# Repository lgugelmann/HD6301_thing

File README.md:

# Exploring the HD6301V1

I recently received a few samples of a Hitachi `HD6301V1` in a DIP-40
package. It's a 1MHz 8bit CPU derived from the Motorola 6801 with a few extra
instructions. It has an onboard mask-programmed 4k ROM, 128 bytes RAM, and 4 I/O
ports that can be used as some combination of data or address bus, or I/O
lines. It also comes with an onboard serial interface. Overall it's a really
neat chip!

- The datasheet for the HD6301v1 can be found
e.g. [here](https://pdf1.alldatasheet.com/datasheet-pdf/view/87402/HITACHI/HD6301V1.html).
- An _extensive_ handbook for the entire Hitachi 6301/6303 series of CPUs,
including copies of all datasheets, can be found on
[archive.org](https://archive.org/details/bitsavers_hitachidateriesHandbook1989_54281821).

This repository contains schematics and code to build a retro-inspired computer
around this chip. The idea is to build this off of modular components and a
shared bus so we can start small and build up piece by piece.

Currently I have a working device with Arduino-like ease of programmability, PS2
keyboard input, HDMI video output. It's complete enough for a working 'Snake'
clone that can be played over both serial console and video out.

## Getting started on a breadboard

The architecture is quite simple and similar to other 8-bit CPUs like
the 6502. There is one 16-bit address bus, one 8-bit data bus, a clock line, a
read/write line, and an interrupt line.

One way in which this chip departs from e.g. a 6502 is that it has several
different 'modes' that affect the memory layout and external buses. Mode
selection is done at startup using the first 3 lines of port 2. After startup
these lines can be reused for other purposes if desired. Mode 1
(non-multiplexed) breaks out all 16 address and 8 data lines. Mode 5 reduces the
external address bus to 8 lines. Mode 0/2/4/6 multiplex the data bus: at the
beginning of the cycle the 8 low address bits are presented, then an address
latch signal fires, then the 8 data bits are set. This frees up one 8-bit port
for I/O. Mode 7 has no external buses at all. Mode 0/5/6/7 map the internal ROM
to the top of the address space. It's inaccessible in 1/2/4. Mode 0 ('test
mode') has a special handling for the first read of the startup vector addresses
at $FFFE/$FFFF: instead of reading them from ROM (as it would in any subsequent
read) they are read over the external bus. This allows one to override the
ROM-interal startup vector while still keeping it accessible otherwise.

By selecting mode 1 at startup it's easy to get this chip to work on a
breadboard by just adding some external parallel RAM / ROM with a bit of address
decoding to select which one to access.

The chip has an internal 4x clock-divider. To get it to run at the max 1MHz you
need a 4MHz oscillator. I had no stability issues on a breadboard even at max
frequency.

The chip requires a minimum 100kHz to run (400kHz oscillator). Going below makes
it unstable.

## Random hardware notes

This is a collection of random notes about the hardware that are either
well-hidden in the datasheet or not documented at all.

- The IRQ line is not specified to be open-drain. It's likely not.
- The reset and standby pins are drawn with Schmitt-trigger inputs in the
  datasheet.
- The datasheet recommends 74'373 chips to latch the address bits in multiplexed
  mode. The '573 is probably a better choice for layout reasons as it has the
  same functionality but instead of having in/out pins next to each other it has
  all 8 inputs on one side and the 8 outputs on the other.
- P21 is not a general purpose I/O pin (even after mode selection). It is either
  a general input, or timer output.
- The mode selection / P2 multiplexing circuit in the datasheet would probably
  not work with a modern '4053 chip. The one in the datasheet has minimum
  switching times higher than the required hold times on the mode selection
  pins. Modern '4053 are faster.
- Reset and power-up are a bit finicky. The datasheet says reset must be held
  low for at least 20ms at power-on time. That's good advice. Without the wait
  time the MCU seems to start working a hair before the power rail reaches
  3V. The clock and data / address lines have their 'high' bits at that voltage
  too. At that point in time a typical 5V ROM might not even have powered up yet
  and you get all sorts of fun non-deterministic behavior. Something like a
  Diodes Inc. `APX811-46` is a great way to satisfy that requirement as it keeps
  reset low after power-up for 100-200ms.  Alternatively, the datasheet seems to
  suggest that the reset line has a Schmitt-trigger input. That would make an RC
  circuit with a long time constant also workable. Have not tried that.
- Exiting the standby mode requires holding reset low 20ms longer than STBY.

## The mask-programmed ROM

The samples I have come mask-programmed with some unknown code. The
`internal_rom` folder contains a dump of that ROM, some very preliminary
disassembly, and details on how to do such a dump using the 'test mode' of the
chip.

The ROM configures the data direction registers of all 4 I/O ports to a
combination of inputs/outputs. This suggests that it was meant to work in
single-chip mode. The MC6801 was popular in automotive applications - maybe this
one was meant to go into a car too.

## Contents of the repository

### Hardware modules

On the hardware side the repository contains
- The main CPU board. This can be used as a fully functional standalone
  single-board computer with 32kB RAM and ROM.
- A programming board to make programming the main CPU board as easy as
  programming an Arduino. This is a Raspberry Pi Pico-based board for USB
  connectivity to a host computer. It can put the main CPU into standby, take
  over the bus, and read or write to RAM/ROM as needed.
- A "video chip" board with HDMI output. This is another Pi Pico-based board
  that implements various graphical modes like a 100x40 or 100x75 text terminal
  with 6-bit color for each foreground and background. On the HDMI side it's
  800x600 pixel. On the bus it presents 64 write-only registers that implement
  various commands like setting characters, colors, or doing cursor moves.

Currently in progress are:
- An audio board based around the OPL3 FM synthesis chips.

### Software

#### HD6301 programs

The 'asm' folder contains software to run on the HD6301. There is a monitor
program for debugging, running other programs, and to provide some basic
libraries for PS2 keyboard handling and more.

There are also various test programs as well as a 'Snake' clone and a simple
audio sequencer.

See the docs in the 'asm' folder for more details.

#### Emulator

The `emulator` folder contains a full-system emulator for the HD6301V1 computer.
It emulates the CPU, I/O, graphics, sound, keyboard, and SD card. See
`emulator/README.md` for details on building and running it.

The emulator includes an extensive test suite with ~314 declarative CPU
instruction tests (in `emulator/testdata/instructions/`) and GoogleTest-based
peripheral tests. Run `ctest` from the build directory to execute all tests.

#### Supporting software

- Much of the glue logic (address decoding, PS2 serial/parallel decoding, etc.)
  is implemented with GreenPAK SLG46826 programmable logic chips (see
  below). The 'greenpak' folder contains a simple python script to program these
  chips via i2c using an FTDI232h breakout board.
- The 'pico\_programmer' and 'pico\_graphics' folders contain the respective
  software for those those chips. The pico programmer has two parts: one to go
  onto the Pi Pico and a Python program to interface with it via serial port to
  do the actual programming.

## Bus documentation

All modules communicate over the following shared bus.

| Pin number | Function            | Notes                                                                        |
|------------|---------------------|------------------------------------------------------------------------------|
| 1..4       | Data bits D0..D3    | Bus users need to coordinate who's driving                                   |
| 5          | 5V                  | Only one device is allowed to power this                                     |
| 6          | GND                 |                                                                              |
| 7..10      | Data bits D4..D7    | Bus users need to coordinate who's driving                                   |
| 11..14     | Address bits A0..A3 | Bus users need to coordinate who's driving                                   |
| 15         | 3.3V                | Only one device is allowed to power this, optional                           |
| 16         | GND                 |                                                                              |
| 17..24     | A4..A11             | Bus users need to coordinate who's driving                                   |
| 25         | GND                 |                                                                              |
| 26         | 3.3V                | Only one device is allowed to power this, optional                           |
| 27..30     | A12..A15            | Bus users need to coordinate who's driving                                   |
| 31         | RX                  | Serial receive as seen from a device on the bus                              |
| 32         | TX                  | Serial transmit as seen from a device on the bus                             |
| 33         | CLK                 | Bus clock                                                                    |
| 34         | R/WB                | Read is high                                                                 |
| 35         | GND                 |                                                                              |
| 36         | 5V                  | Only one device is allowed to power this                                     |
| 37         | C1                  | Control line 1, up to the exact devices on the bus to decide what this does. |
| 38         | C2                  | Control line 2, up to the exact devices on the bus to decide what this does. |
| 39         | RESETB              | Active low reset. Open drain. Pullup on CPU board.                           |
| 40         | IRQB                | Active low interrupt. Open drain. Pullup on CPU board.                       |

This is 40 pins as it's easy to find 40pin IDC connectors and ribbon cables. The
power / GND pins are mirrored so that an upside-down connector has them in the
same place.

There are no chip select pins. Additional boards that want to fit into specific
parts of the memory map need to decode the address pins on their board and
coordinate with everyone else. Programmable GreenPAKs make this easy enough.

Pins are all push-pull unless stated otherwise. Any shared use needs to be
coordinated.

Logic levels are assumed 5V CMOS.

This is not how one designs for signal integrity - but it works well enough for
me. The user-friendliness of getting a ribbon cable to a breadboard to prototype
the next module is the overriding concern here.

### Bus details for HD6301 board

| Pin number | Function | Notes                                                                            |
|------------|----------|----------------------------------------------------------------------------------|
| 38         | STBYB    | Active low standby signal. For Pico Programmer to make HD6301 let go of the bus. |

## Work log

This section contains possible projects and the state of the current in-progress
pieces of work.

### Faster SD card reads

The next goal is to get faster SD card reads as described in `asm/README.md`.
This means emulating the schematic in `io_board` in the emulator.

Tasks:

- Emulator:
  - ~~Create basic shift register output support in W65C22~~
  - ~~Figure out how to emulate clock inversion and delay~~
  - ~~Emulate a serial-in, parallel-out shift register like 74'164 series.~~
  - ~~Connect the above two pieces in-between the W65C22 and the current SPI emulation.~~
- ASM
  - ~~Update the code to use SR instead of bit-banging on a port for SPI~~
- Hardware
  - ~~Actually try the approach in real hardware~~ \[done, down to ~10ms\]
  - Write out schematics and design the board

### Documentation and repository cleanup

Any day now! This README file is badly outdated vs the state of the project. It
doesn't mention the emulator at all for example. The various hardware modules
should also be listed and better documented.

Tasks:

- Pick a standard for how to structure the individual module folders and stick to it
  - Put a README.md with each module, and document all known hardware issues.
  - I don't like the catch-all `greenpak` folder. That should go with the modules.
- Get rid of the `ft231x_programmer` stuff. It's an early idea that's now badly
  outdated.
- Rename `board` to something better.
- Add README.md to the `tools` folder.
- Update this file with a better overall description. It's very very out of date.

### General ASM improvements

Tasks:

- Define and implement a standard for error reporting. With FAT16, MIDI decoding
  etc there is some complex logic that could benefit from a standard way to pass
  around errors and refer to standard error strings for them.

### FAT16 improvements

The current FAT16 code is read-only and is limited to using only one sector of
FAT (so only 254 clusters). This is not an actual limitation yet. The APIs are a
bit wonky, the error reporting inconsistent.

Tasks:

- Implement write support
  - Goal: Snake should get persistent high scores.
- Implement support for using more than just the first FAT sector

### Expanding the programmer board to be a runtime monitor thing too

Right now the programmer board has the ability to read almost the entire bus
(data, address, IRQ), but we're not doing anything with that. An idea would be
to also plumb CLK back to the Pico and very quickly sample the bus on clock
edges. Wiring-wise this should be possible on the existing board by changing the
GreenPAK setup - the C1 pin is unused on the Pico side.

It's not clear that we can do this fast enough (easily), but it's worth trying
out. It's probably very much possible to do the hard way as we can bit-bang at
400+MHz for the DVI out using PIO.

Some math:

- The internets claim that Pico interrupt latency can be brought down to
  100-200ns. A busy-loop on the pin state ~70ns.
- The LVC245 in use take 10ns max to go from OE to data available.
- No idea how fast one can read 8 data pins - but probably tens of ns. Say 50 as
  an upper bound.

If we take some upper bounds we get 200 trigger + 3 * (10 + 50) ~= 400ns. We
have 500ns budget between clock edges so this sounds doable. Afterwards we have
500 more ns to do some data processing until the next interesting edge.

Assume we have ~100k of RAM free (total 264k, seems reasonable). If we store 3
bytes per clock cycle we get roughly 30ms of data in a buffer before we run
over. In total we generate 3MB/s. Getting those off the Pico in a continuous
fashion does not seem doable without trickery. The theoretical maximum is
12Mbit/s, or 1.5MB/sec. In practice folks seem to get somewhere between 500 and
850 KiB/sec. The minimum information needed to code the instructions would be:
instruction, address (if needed), data. A 3-byte instruction typically takes 4
cycles and would have 4 bytes of data total (1 instruction, 2 address, 1
data). We'd get a factor 3 compression here if that's the average case. It might
just barely be possible to stream things continuously.

Tasks:

- Rework the GreenPAK setup to get the clock back to a Pico input pin.
- See how fast the IRQ triggers and whether we can sample the bus on time.

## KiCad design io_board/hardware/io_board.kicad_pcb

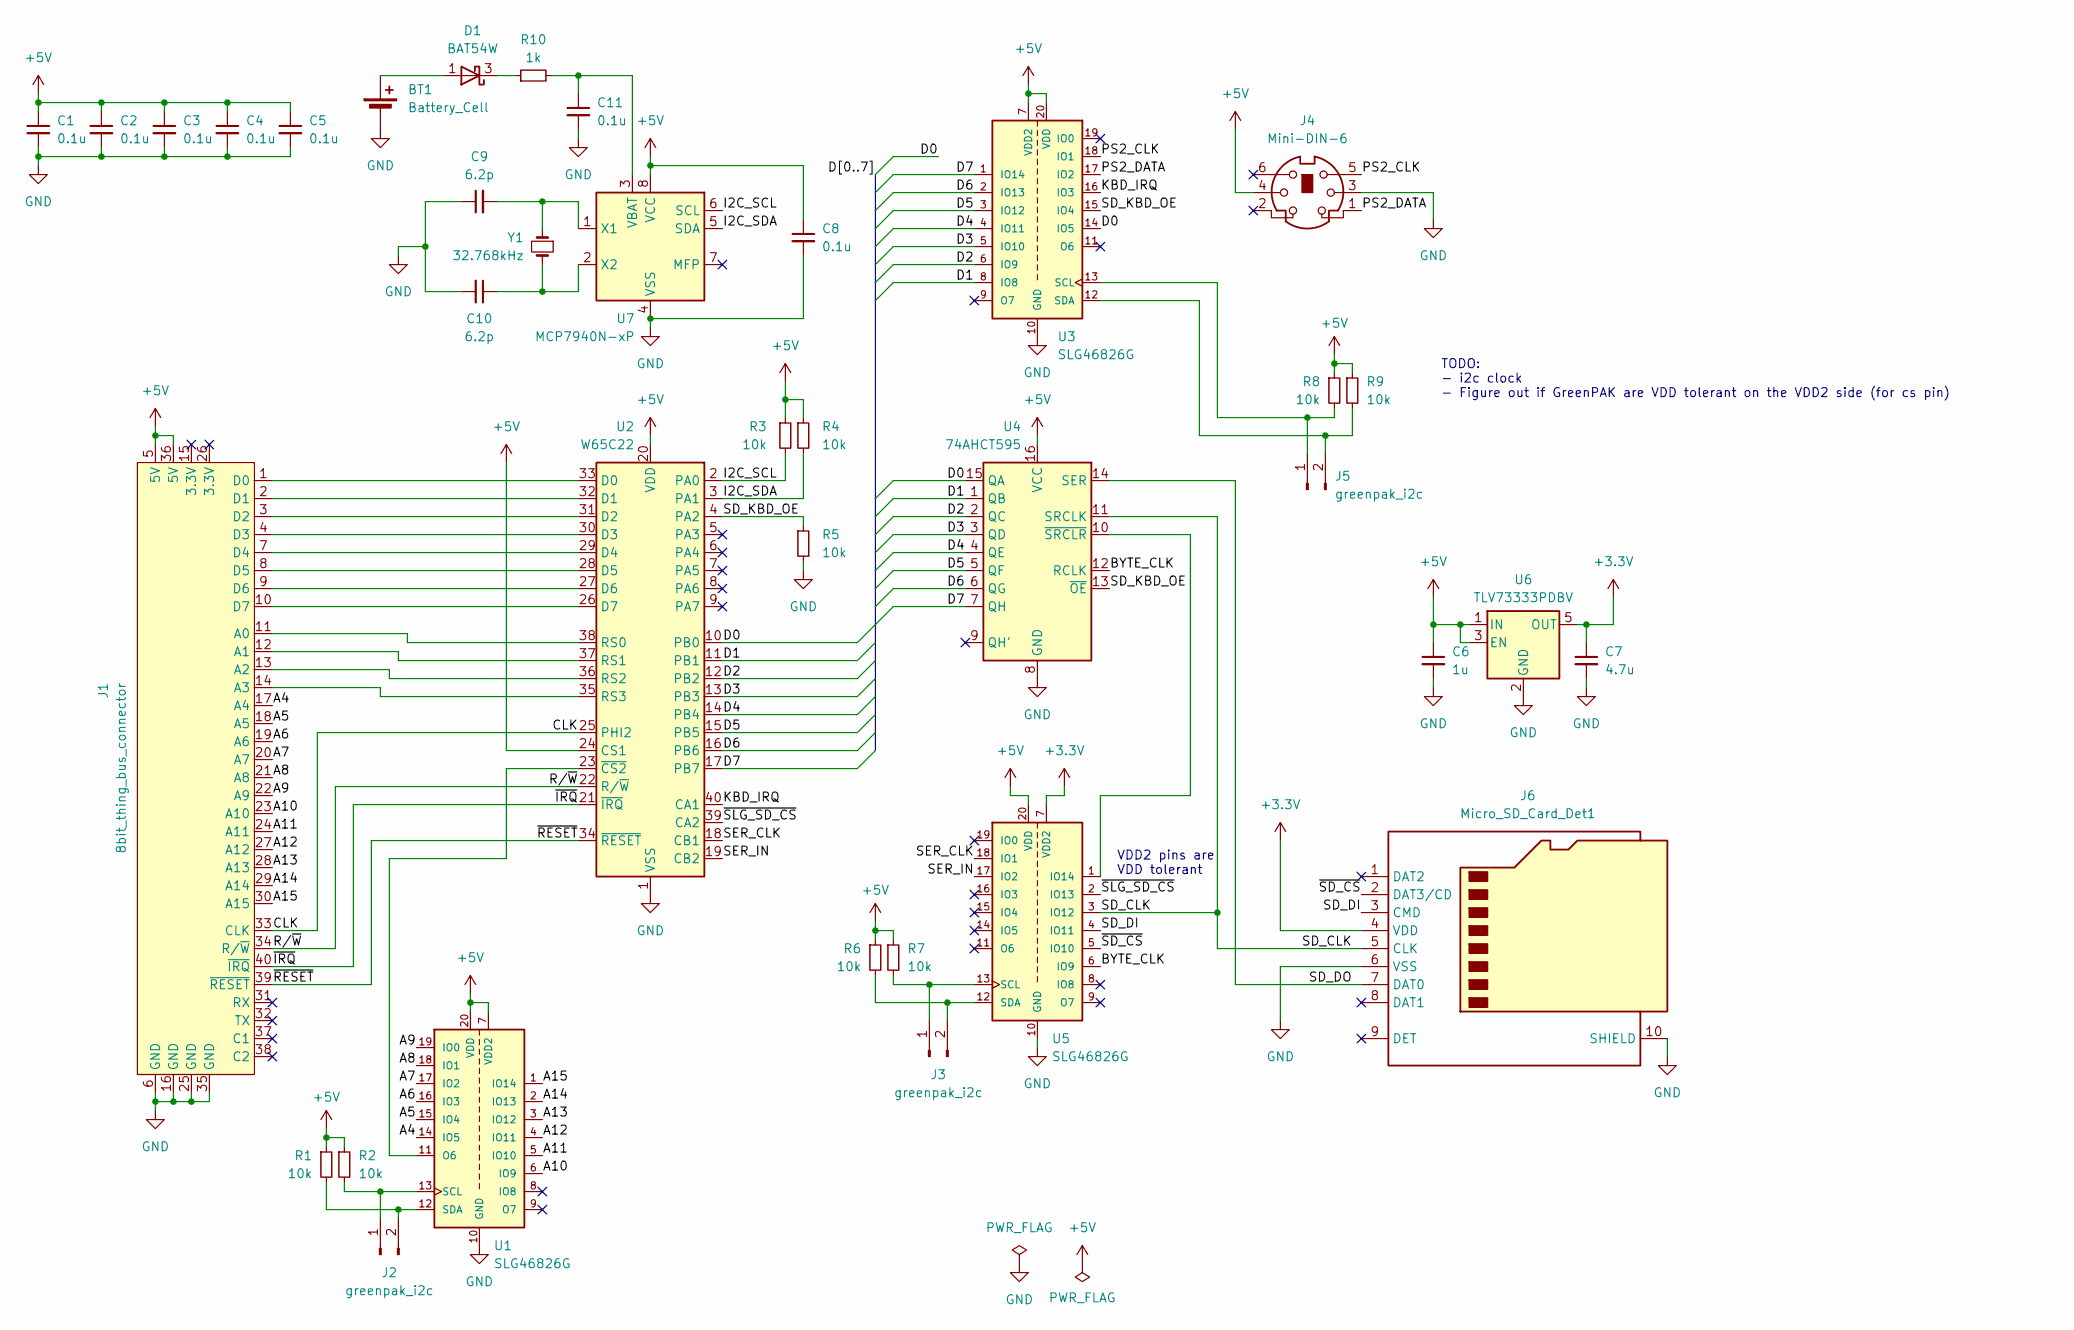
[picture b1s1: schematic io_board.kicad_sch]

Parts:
BT1: Battery_Cell; BatteryHolder_MPD_BC2003_1x2032
C1, C2, C3, C4, C5, C8, C11: 0.1u; C_0805_2012Metric_Pad1.18x1.45mm_HandSolder
C6: 1u; C_0805_2012Metric_Pad1.18x1.45mm_HandSolder
C7: 4.7u; C_0805_2012Metric_Pad1.18x1.45mm_HandSolder
C9, C10: 6.2p; C_0805_2012Metric_Pad1.18x1.45mm_HandSolder
D1: BAT54W; SOT-323_SC-70
J1: 8bit_thing_bus_connector; IDC-Header_2x20_P2.54mm_Horizontal
J2, J3, J5: greenpak_i2c; PinHeader_1x02_P2.54mm_Vertical_minimal
J4: Mini-DIN-6; KMDGX6SBS
J6: Micro_SD_Card_Det1; microSD_HC_Hirose_DM3D-SF
R1, R2, R3, R4, R5, R6, R7, R8, R9: 10k; R_0805_2012Metric_Pad1.20x1.40mm_HandSolder
R10: 1k; R_0805_2012Metric_Pad1.20x1.40mm_HandSolder
U1, U3, U5: SLG46826G; SOP65P640X120-20N; PARTREV 3.10
U2: W65C22; DIP-40_W15.24mm
U4: 74AHCT595; TSSOP-16_4.4x5mm_P0.65mm
U6: TLV73333PDBV; SOT-23-5
U7: MCP7940N-xP; DIP-8_W7.62mm
Y1: 32.768kHz; Crystal_C26-LF_D2.1mm_L6.5mm_Horizontal

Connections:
+3.3V: C7.1, J6.4 (VDD), U5.7 (VDD2), U6.5 (OUT)
+5V: C1.1, C2.1, C3.1, C4.1, C5.1, C6.1, C8.1, J1.5 (5V), J1.36 (5V), J4.4, R1.1, R2.1, R3.1, R4.1, R6.1, R7.1, R8.1, R9.1, U1.7 (VDD2), U1.20 (VDD), U2.20 (VDD), U2.24 (CS1), U3.7 (VDD2), U3.20 (VDD), U4.16 (VCC), U5.20 (VDD), U6.1 (IN), U6.3 (EN), U7.8 (VCC)
/A4: J1.17 (A4), U1.14 (IO5)
/A5: J1.18 (A5), U1.15 (IO4)
/A6: J1.19 (A6), U1.16 (IO3)
/A7: J1.20 (A7), U1.17 (IO2)
/A8: J1.21 (A8), U1.18 (IO1)
/A9: J1.22 (A9), U1.19 (IO0)
/A10: J1.23 (A10), U1.6 (IO9)
/A11: J1.24 (A11), U1.5 (IO10)
/A12: J1.27 (A12), U1.4 (IO11)
/A13: J1.28 (A13), U1.3 (IO12)
/A14: J1.29 (A14), U1.2 (IO13)
/A15: J1.30 (A15), U1.1 (IO14)
/BYTE_CLK: U4.12 (RCLK), U5.6 (IO9)
/CLK: J1.33 (CLK), U2.25 (PHI2)
/D0: U2.10 (PB0), U3.14 (IO5), U4.15 (QA)
/D1: U2.11 (PB1), U3.8 (IO8), U4.1 (QB)
/D2: U2.12 (PB2), U3.6 (IO9), U4.2 (QC)
/D3: U2.13 (PB3), U3.5 (IO10), U4.3 (QD)
/D4: U2.14 (PB4), U3.4 (IO11), U4.4 (QE)
/D5: U2.15 (PB5), U3.3 (IO12), U4.5 (QF)
/D6: U2.16 (PB6), U3.2 (IO13), U4.6 (QG)
/D7: U2.17 (PB7), U3.1 (IO14), U4.7 (QH)
/I2C_SCL: R3.2, U2.2 (PA0), U7.6 (SCL)
/I2C_SDA: R4.2, U2.3 (PA1), U7.5 (SDA)
/KBD_IRQ: U2.40 (CA1), U3.16 (IO3)
/PS2_CLK: J4.5, U3.18 (IO1)
/PS2_DATA: J4.1, U3.17 (IO2)
/R/~W: J1.34 (R/~W), U2.22 (R/~W)
/SD_CLK: J6.5 (CLK), U4.11 (SRCLK), U5.3 (IO12)
/SD_DI: J6.3 (CMD), U5.4 (IO11)
/SD_DO: J6.7 (DAT0), U4.14 (SER)
/SD_KBD_OE: R5.1, U2.4 (PA2), U3.15 (IO4), U4.13 (~OE)
/SER_CLK: U2.18 (CB1), U5.18 (IO1)
/SER_IN: U2.19 (CB2), U5.17 (IO2)
/~IRQ: J1.40 (~IRQ), U2.21 (~IRQ)
/~RESET: J1.39 (~RESET), U2.34 (~RESET)
/~SD_CS: J6.2 (DAT3/CD), U5.5 (IO10)
/~SLG_SD_CS: U2.39 (CA2), U5.2 (IO13)
GND: BT1.2 (-), C1.2, C2.2, C3.2, C4.2, C5.2, C6.2, C7.2, C8.2, C9.1, C10.2, C11.2, J1.6 (GND), J1.16 (GND), J1.25 (GND), J1.35 (GND), J4.3, J6.6 (VSS), J6.10 (SHIELD), R5.2, U1.10 (GND), U2.1 (VSS), U3.10 (GND), U4.8 (GND), U5.10 (GND), U6.2 (GND), U7.4 (VSS)
unnamed: BT1.1 (+), D1.1 (A)
unnamed: D1.3 (K), R10.1
unnamed: J1.11 (A0), U2.38 (RS0)
unnamed: J1.12 (A1), U2.37 (RS1)
unnamed: J1.13 (A2), U2.36 (RS2)
unnamed: J1.14 (A3), U2.35 (RS3)
unnamed: J1.1 (D0), U2.33 (D0)
unnamed: J1.2 (D1), U2.32 (D1)
unnamed: J1.3 (D2), U2.31 (D2)
unnamed: J1.4 (D3), U2.30 (D3)
unnamed: J1.7 (D4), U2.29 (D4)
unnamed: J1.8 (D5), U2.28 (D5)
unnamed: J1.9 (D6), U2.27 (D6)
unnamed: J1.10 (D7), U2.26 (D7)
unnamed: J2.1, R2.2, U1.13 (SCL)
unnamed: J2.2, R1.2, U1.12 (SDA)
unnamed: J3.1, R7.2, U5.13 (SCL)
unnamed: J3.2, R6.2, U5.12 (SDA)
unnamed: J5.1, R8.2, U3.13 (SCL)
unnamed: J5.2, R9.2, U3.12 (SDA)
unnamed: U1.11 (O6), U2.23 (~CS2)
unnamed: U4.10 (~SRCLR), U5.1 (IO14)
unnamed: C11.1, R10.2, U7.3 (VBAT)
unnamed: C9.2, U7.1 (X1), Y1.1
unnamed: C10.1, U7.2 (X2), Y1.2

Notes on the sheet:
TODO: - i2c clock - Figure out if GreenPAK are VDD tolerant on the VDD2 side (for cs pin)
VDD2 pins are VDD tolerant

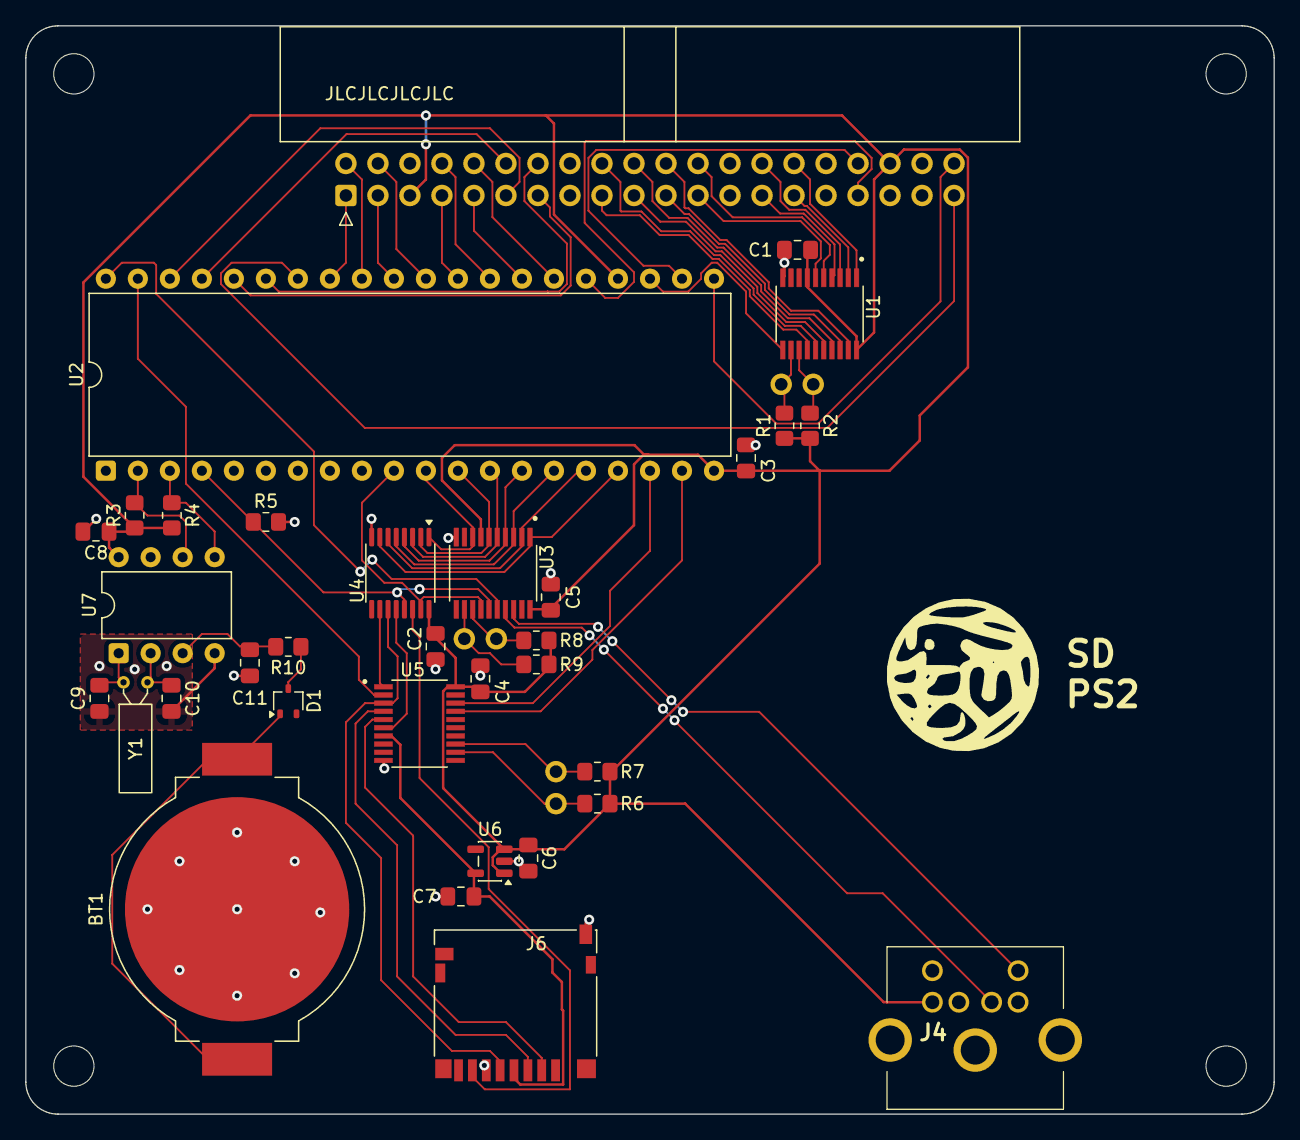
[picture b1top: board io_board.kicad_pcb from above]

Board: 2 copper layers, 99.1 x 86.4 mm, 37 parts (0 on the bottom side), 66 nets.

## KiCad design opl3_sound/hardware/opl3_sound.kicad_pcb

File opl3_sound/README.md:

# OPL3 sound board

## Hardware

This board contains OPL3 chips: YMF262 (the digital FM sound chip) and its
compainon YAC512 digital-analog-converter. It also has a mono amplifier for a
small speaker and a stereo one for headphones. Plugging headphones in/out
switches from spaker to headphones or back.

### Quirks and possible gotchas

- Writes are triggered on the *rising* edge of WR/CS (whichever is first)

#### Timer interrupts

The OPL3 datasheet omits to mention that when writing a 1 to the `RST` bit in
register `$04`, all other bits are ignored.

This is convenient as it allows IRQ routines to clear the interrupt without
needing to keep track of the rest of the register.

#### Hardware notes / bugs in v2

- Volume doesn't go all the way down
- Forgot pullups for i2c on GreenPAK

## Software

There is a small utility `opl3.py` to interface with the OPL3 board via serial
port. This requires the `serial_opl3` program to be running on the 6301 thing.

The most interesting functionality is probably `opl3.py play [vgm file]` which
plays a VGM file intended for OPL3 on the sound board.

The rest of the functionality is probably in various states of disrepair. It was
used for board bring-up and early testing and not maintained since.

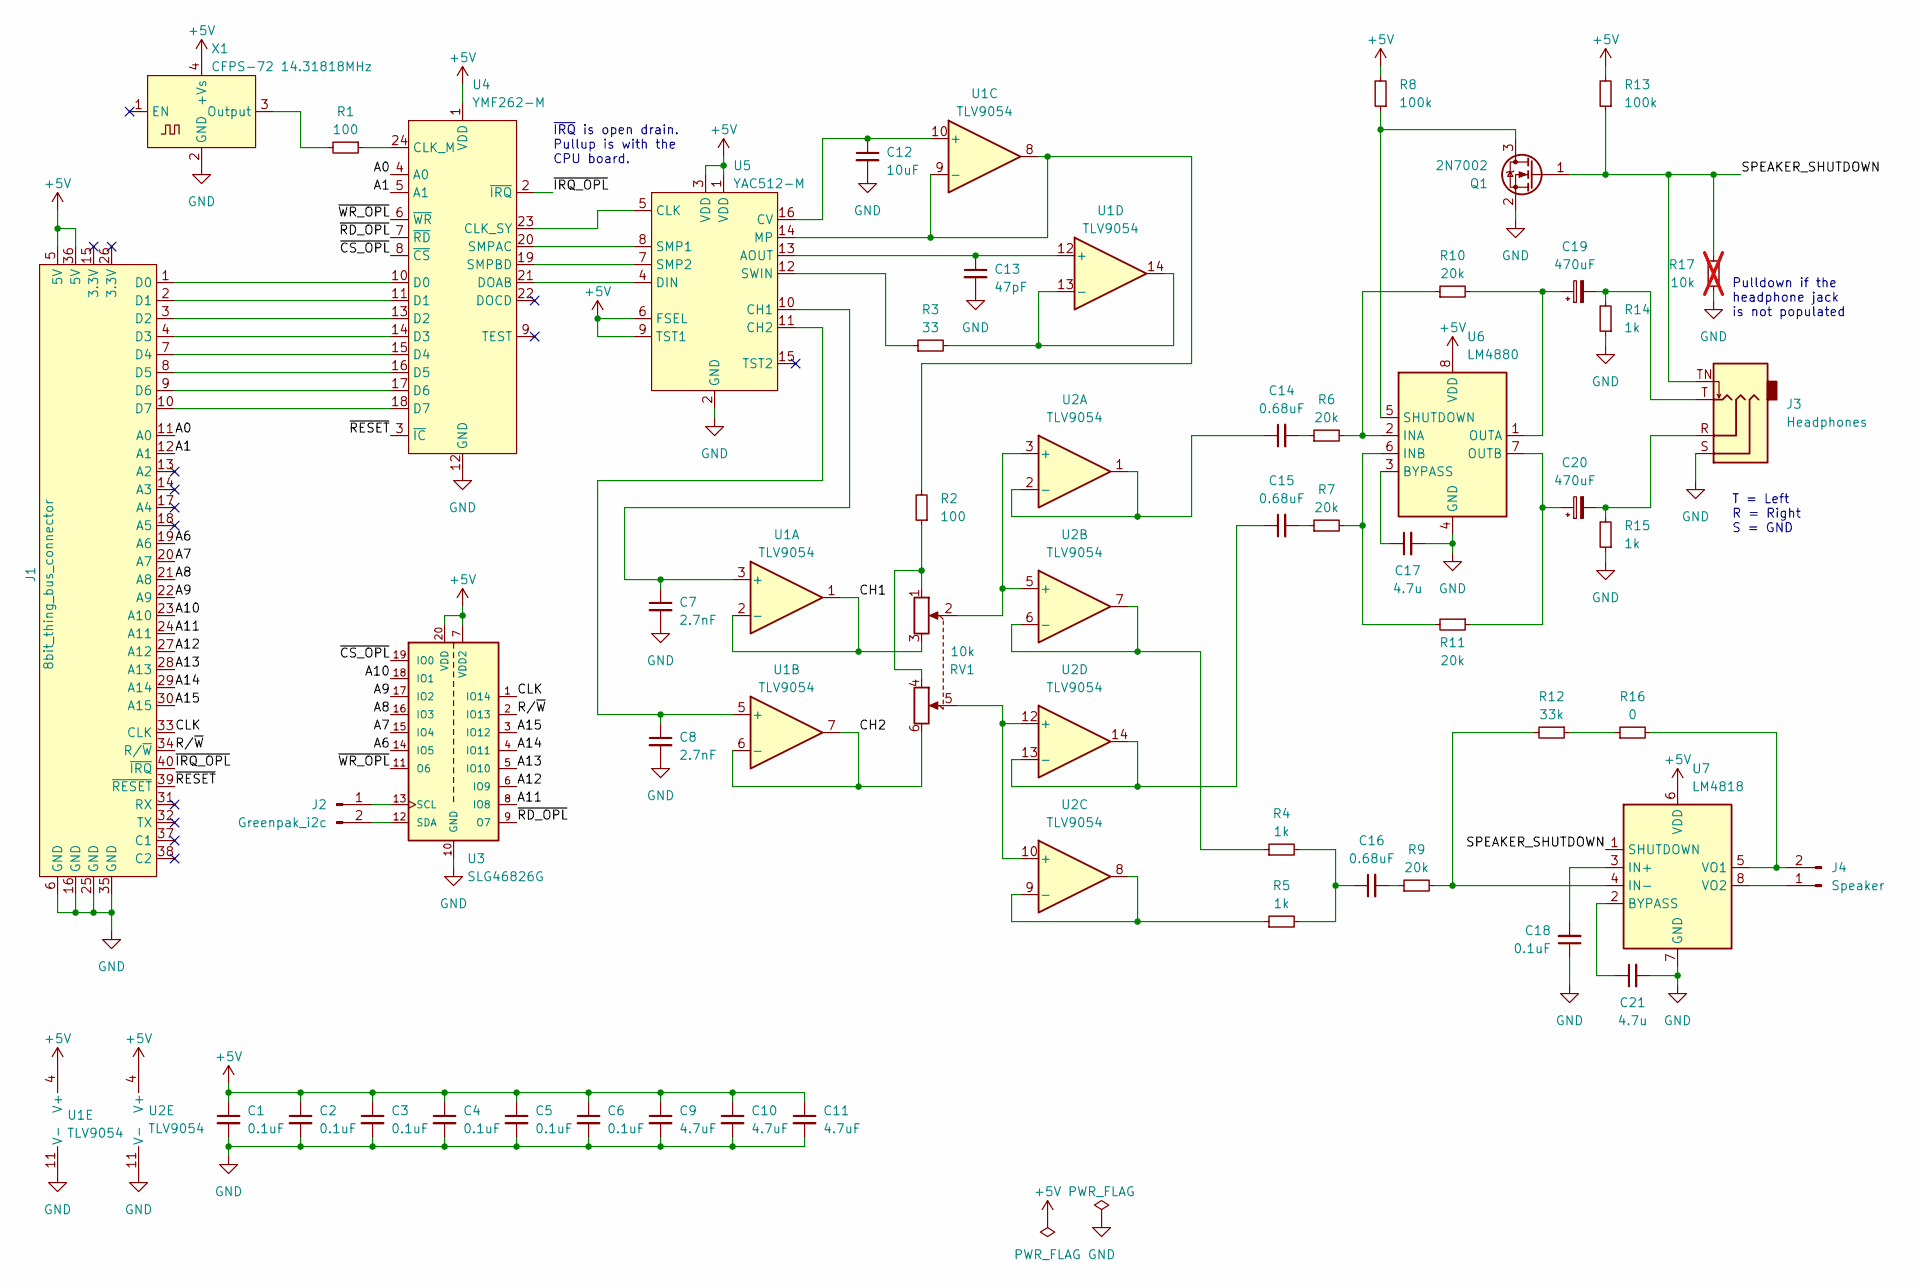
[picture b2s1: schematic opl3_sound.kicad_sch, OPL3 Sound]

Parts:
C1, C2, C3, C4, C5, C6, C18: 0.1uF; C_0805_2012Metric_Pad1.18x1.45mm_HandSolder
C7, C8: 2.7nF; C_0805_2012Metric_Pad1.18x1.45mm_HandSolder
C9, C10, C11: 4.7uF; C_0805_2012Metric_Pad1.18x1.45mm_HandSolder
C12: 10uF; C_0805_2012Metric_Pad1.18x1.45mm_HandSolder
C13: 47pF; C_0805_2012Metric_Pad1.18x1.45mm_HandSolder
C14, C15, C16: 0.68uF; C_Rect_L7.2mm_W4.5mm_P5.00mm_FKS2_FKP2_MKS2_MKP2
C17, C21: 4.7u; C_0805_2012Metric_Pad1.18x1.45mm_HandSolder
C19, C20: 470uF; CP_Radial_D8.0mm_P3.50mm
J1: 8bit_thing_bus_connector; IDC-Header_2x20_P2.54mm_Horizontal
J2: Greenpak_i2c; PinHeader_1x02_P2.54mm_Vertical_minimal
J3: Headphones; Jack_3.5mm_CUI_SJ-3524-SMT_Horizontal
J4: Speaker; PinHeader_1x02_P2.54mm_Horizontal
Q1: 2N7002; SOT-23_Handsoldering
R1, R2: 100; R_0805_2012Metric_Pad1.20x1.40mm_HandSolder
R3: 33; R_0805_2012Metric_Pad1.20x1.40mm_HandSolder
R4, R5, R14, R15: 1k; R_0805_2012Metric_Pad1.20x1.40mm_HandSolder
R6, R7, R9, R10, R11: 20k; R_0805_2012Metric_Pad1.20x1.40mm_HandSolder
R8, R13: 100k; R_0805_2012Metric_Pad1.20x1.40mm_HandSolder
R12: 33k; R_0805_2012Metric_Pad1.20x1.40mm_HandSolder
R16: 0; R_0805_2012Metric_Pad1.20x1.40mm_HandSolder
R17: 10k; R_0805_2012Metric_Pad1.20x1.40mm_HandSolder; not fitted
RV1: 10k; PTD9022015KA104
U1, U2: TLV9054; SOIC-14_3.9x8.7mm_P1.27mm
U3: SLG46826G; SOP65P640X120-20N; PARTREV 3.10
U4: YMF262-M; SOP-24_8.4x15.5mm_P1.27mm
U5: YAC512-M; SOIC-16W_5.3x10.2mm_P1.27mm
U6: LM4880; SOIC-8_3.9x4.9mm_P1.27mm
U7: LM4818; SOIC-8_3.9x4.9mm_P1.27mm
X1: CFPS-72 14.31818MHz; Oscillator_SMD_IQD_IQXO70-4Pin_7.5x5.0mm_HandSoldering

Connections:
+5V: C1.1, C2.1, C3.1, C4.1, C5.1, C6.1, C9.1, C10.1, C11.1, J1.5 (5V), J1.36 (5V), R8.2, R13.2, U1.4 (V+), U2.4 (V+), U3.7 (VDD2), U3.20 (VDD), U4.1 (VDD), U5.1 (VDD), U5.3 (VDD), U5.6 (FSEL), U5.9 (TST1), U6.8 (VDD), U7.6 (VDD), X1.4 (+Vs)
/A0: J1.11 (A0), U4.4 (A0)
/A1: J1.12 (A1), U4.5 (A1)
/A6: J1.19 (A6), U3.14 (IO5)
/A7: J1.20 (A7), U3.15 (IO4)
/A8: J1.21 (A8), U3.16 (IO3)
/A9: J1.22 (A9), U3.17 (IO2)
/A10: J1.23 (A10), U3.18 (IO1)
/A11: J1.24 (A11), U3.8 (IO8)
/A12: J1.27 (A12), U3.6 (IO9)
/A13: J1.28 (A13), U3.5 (IO10)
/A14: J1.29 (A14), U3.4 (IO11)
/A15: J1.30 (A15), U3.3 (IO12)
/CH1: RV1.3, U1.1, U1.2 (-)
/CH2: RV1.6, U1.6 (-), U1.7
/CLK: J1.33 (CLK), U3.1 (IO14)
/R/~W: J1.34 (R/~W), U3.2 (IO13)
/SPEAKER_SHUTDOWN: J3.TN, Q1.1 (G), R13.1, R17.1, U7.1 (SHUTDOWN)
/~CS_OPL: U3.19 (IO0), U4.8 (~CS)
/~IRQ_OPL: J1.40 (~IRQ), U4.2 (~IRQ)
/~RD_OPL: U3.9 (O7), U4.7 (~RD)
/~RESET: J1.39 (~RESET), U4.3 (~IC)
/~WR_OPL: U3.11 (O6), U4.6 (~WR)
GND: C1.2, C2.2, C3.2, C4.2, C5.2, C6.2, C7.2, C8.2, C9.2, C10.2, C11.2, C12.2, C13.2, C17.2, C18.1, C21.2, J1.6 (GND), J1.16 (GND), J1.25 (GND), J1.35 (GND), J3.S, Q1.2 (S), R14.1, R15.1, R17.2, U1.11 (V-), U2.11 (V-), U3.10 (GND), U4.12 (GND), U5.2 (GND), U6.4 (GND), U7.7 (GND), X1.2 (GND)
unnamed: C14.2, R6.1
unnamed: C15.2, R7.1
unnamed: C16.1, R4.2, R5.2
unnamed: C16.2, R9.1
unnamed: C19.2, J3.T, R14.2
unnamed: C20.2, J3.R, R15.2
unnamed: J1.1 (D0), U4.10 (D0)
unnamed: J1.2 (D1), U4.11 (D1)
unnamed: J1.3 (D2), U4.13 (D2)
unnamed: J1.4 (D3), U4.14 (D3)
unnamed: J1.7 (D4), U4.15 (D4)
unnamed: J1.8 (D5), U4.16 (D5)
unnamed: J1.9 (D6), U4.17 (D6)
unnamed: J1.10 (D7), U4.18 (D7)
unnamed: J2.1, U3.13 (SCL)
unnamed: J2.2, U3.12 (SDA)
unnamed: J4.1, U7.8 (VO2)
unnamed: J4.2, R16.2, U7.5 (VO1)
unnamed: Q1.3 (D), R8.1, U6.5 (SHUTDOWN)
unnamed: R2.1, RV1.1, RV1.4
unnamed: R12.1, R16.1
unnamed: C7.1, U1.3 (+), U5.10 (CH1)
unnamed: C8.1, U1.5 (+), U5.11 (CH2)
unnamed: C12.1, U1.10 (+), U5.16 (CV)
unnamed: R2.2, U1.8, U1.9 (-), U5.14 (MP)
unnamed: C13.1, U1.12 (+), U5.13 (AOUT)
unnamed: R3.2, U1.13 (-), U1.14
unnamed: RV1.2, U2.3 (+), U2.5 (+)
unnamed: C14.1, U2.1, U2.2 (-)
unnamed: R4.1, U2.6 (-), U2.7
unnamed: RV1.5, U2.10 (+), U2.12 (+)
unnamed: R5.1, U2.8, U2.9 (-)
unnamed: C15.1, U2.13 (-), U2.14
unnamed: R1.1, U4.24 (CLK_M)
unnamed: U4.23 (CLK_SY), U5.5 (CLK)
unnamed: U4.21 (DOAB), U5.4 (DIN)
unnamed: U4.20 (SMPAC), U5.8 (SMP1)
unnamed: U4.19 (SMPBD), U5.7 (SMP2)
unnamed: R3.1, U5.12 (SWIN)
unnamed: C17.1, U6.3 (BYPASS)
unnamed: R6.2, R10.1, U6.2 (INA)
unnamed: R7.2, R11.2, U6.6 (INB)
unnamed: C19.1, R10.2, U6.1 (OUTA)
unnamed: C20.1, R11.1, U6.7 (OUTB)
unnamed: C21.1, U7.2 (BYPASS)
unnamed: C18.2, U7.3 (IN+)
unnamed: R9.2, R12.2, U7.4 (IN-)
unnamed: R1.2, X1.3 (Output)

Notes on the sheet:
Pulldown if the headphone jack is not populated
~{IRQ} is open drain. Pullup is with the CPU board.
T = Left R = Right S = GND

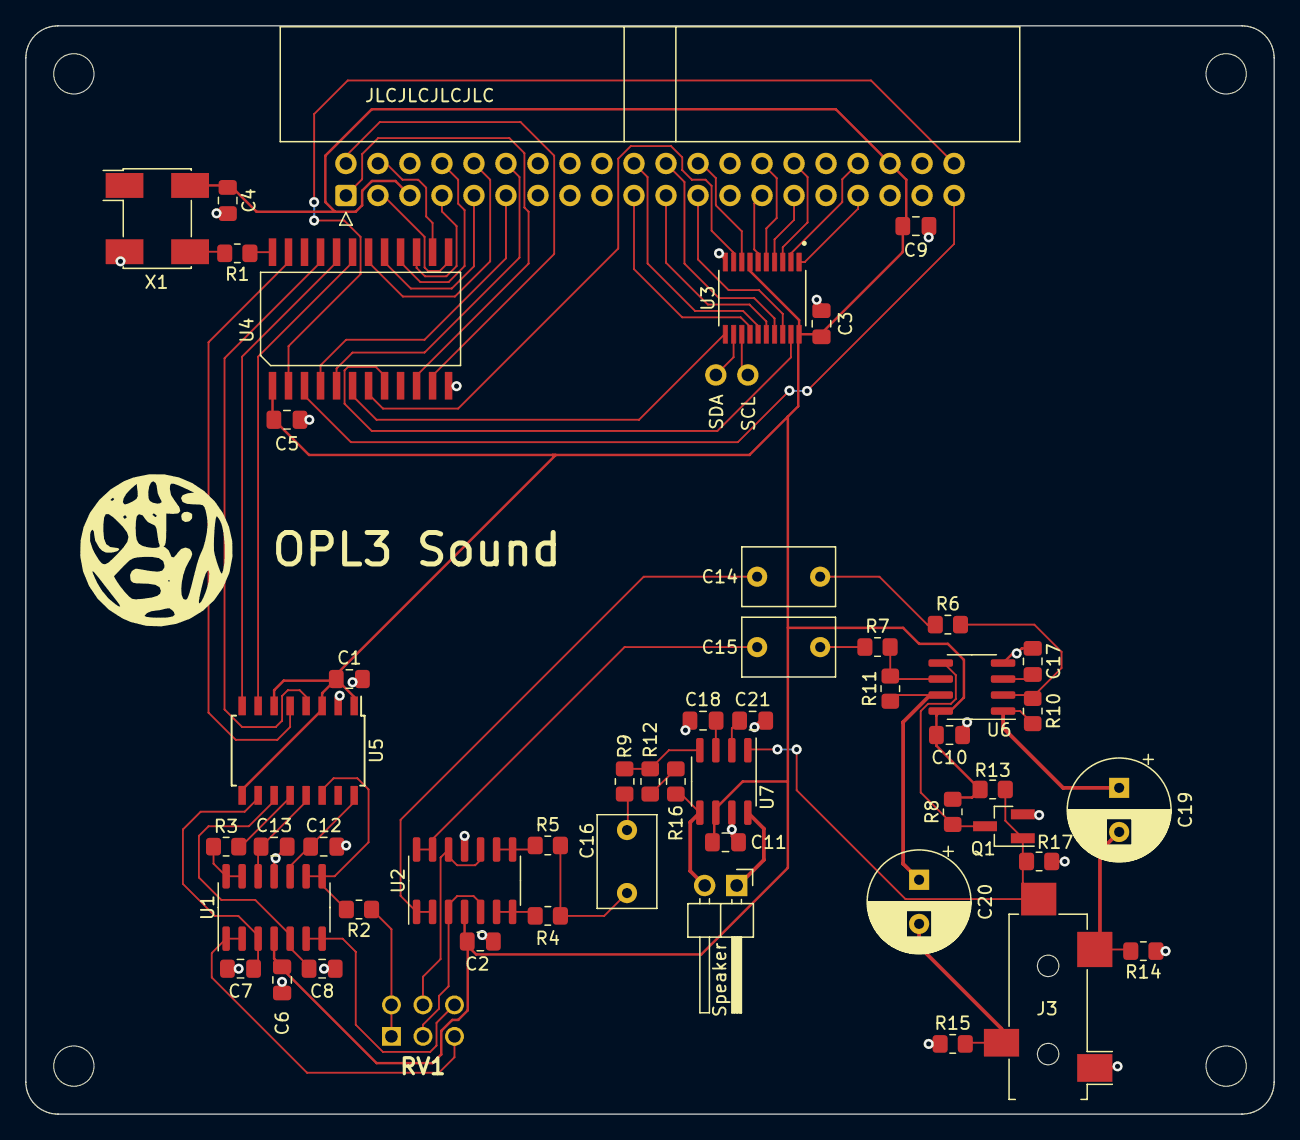
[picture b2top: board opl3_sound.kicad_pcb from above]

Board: 2 copper layers, 99.1 x 86.4 mm, 52 parts (0 on the bottom side), 72 nets.
